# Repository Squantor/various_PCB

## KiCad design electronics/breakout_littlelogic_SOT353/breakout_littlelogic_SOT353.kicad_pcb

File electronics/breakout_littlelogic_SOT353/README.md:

# Little logic breakout for 5 pin SOT353 packages
Simple breakout board for little logic devices in SOT353 case.
## TODO's
Still some things need to be done:
* schematic entry 
* PCB layout
* Review with one night in between
* Produce at [OSHPARK](https://oshpark.com/)
* Assemble
* Test & characterise
* update Readme.md with pictures and BOM
## BOM
* any 5 pin little logic in SOT353 has this pinout with VDD/VSS in these positions

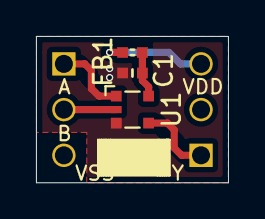
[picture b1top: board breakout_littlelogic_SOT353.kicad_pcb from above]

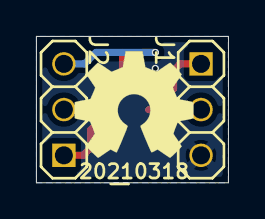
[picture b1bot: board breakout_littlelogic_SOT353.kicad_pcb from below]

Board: 2 copper layers, 10.7 x 8.1 mm, 8 parts (4 on the bottom side), 6 nets.

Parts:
C1: 1u; C_0402
FB1: 600; L_0402
J1, J2: Conn_01x03; Header-0254-1X03-H010
N1: 20210318; Label_Generic
N2: OHWLOGO; OSHW-Symbol_6.7x6mm_SilkScreen
N3: Type; Label_Note_small
U1: Generic_LL_5pin; SOT353

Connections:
/A: J1.1, U1.1
/B: J1.2, U1.2
/VDD: FB1.2, J2.3
/VSS: C1.2, J1.3, U1.3
/Y: J2.1, U1.4
unnamed: C1.1, FB1.1, U1.5

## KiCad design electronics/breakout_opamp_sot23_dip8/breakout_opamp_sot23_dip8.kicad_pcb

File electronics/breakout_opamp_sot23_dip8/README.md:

# SOT23-5 opamp to PDIP-8 converter
Small converter PCB that converts a SOT23-5 opamp to a PDIP-8 footprint
## TODO's
Still some things need to be done:
* Fill in this project description
* schematic entry 
* PCB layout
* Review with one night in between
* Produce at [OSHPARK](https://oshpark.com/)
* Assemble
* Test & characterise
* update Readme.md with pictures and BOM
## BOM
This is a list of hardware components. If just mentioned a generic component like a 1K 0402 resistor, just name it as such, free to substitute. If you need some special integrated IC's show some sources like Mouser, Digikey, Farnell, or LCSC
* Generic SOT23-5 opamp like LM321
## Pictures

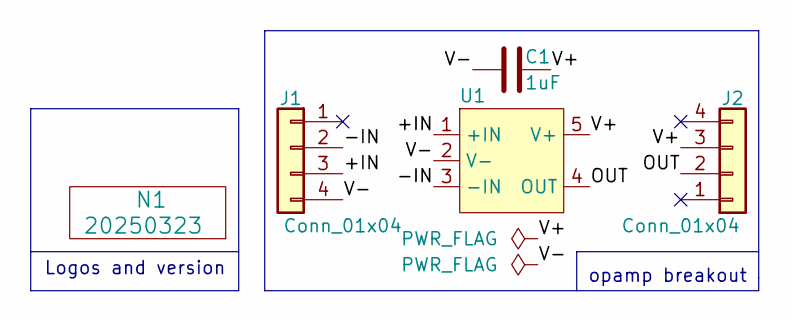
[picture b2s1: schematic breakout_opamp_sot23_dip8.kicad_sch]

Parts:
C1: 1uF; C_0805+0603
J1, J2: Conn_01x04; Header-0254-1X04-H010
N1: 20250323; Label_Generic
U1: SOT23-5-Microchip-OT

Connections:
/+IN: J1.3, U1.1 (+IN)
/-IN: J1.2, U1.3 (-IN)
/OUT: J2.2, U1.4 (OUT)
/V+: C1.2, J2.3, U1.5 (V+)
/V-: C1.1, J1.4, U1.2 (V-)

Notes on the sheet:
Logos and version
opamp breakout

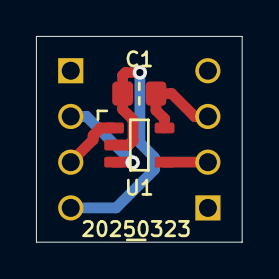
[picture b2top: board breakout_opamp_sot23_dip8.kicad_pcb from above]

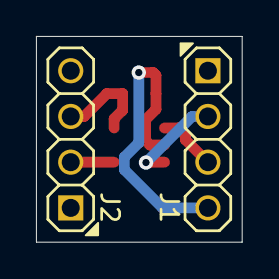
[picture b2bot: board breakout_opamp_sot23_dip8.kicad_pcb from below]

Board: 2 copper layers, 11.4 x 11.4 mm, 5 parts (2 on the bottom side), 5 nets.

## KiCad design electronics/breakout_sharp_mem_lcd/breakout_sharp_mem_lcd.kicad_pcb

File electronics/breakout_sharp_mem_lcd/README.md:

# Sharp memory LCD breakout board
Breakout board to test out sharp memory LCD support circuits.
## TODO's
* Review with one night in between
* Produce
* Assemble
* Test & characterise
* update Readme.md with pictures and BOM
## BOM
* [REG710NA-5/3K](https://www.lcsc.com/product-detail/DC-DC-Converters_Texas-Instruments-REG710NA-5-3K_C527422.html) 5V output regulated charge pump.
* Any sharp memory LCD, I get them at this [aliexpress store](https://www.aliexpress.com/store/5497024?spm=a2g0s.9042311.0.0.4f7e4c4d0shfdY).
* [THD0515-10CL-SN](https://www.lcsc.com/product-detail/FFC-FPC-Connectors_THD-THD0515-10CL-SN_C283142.html) flat flex connector

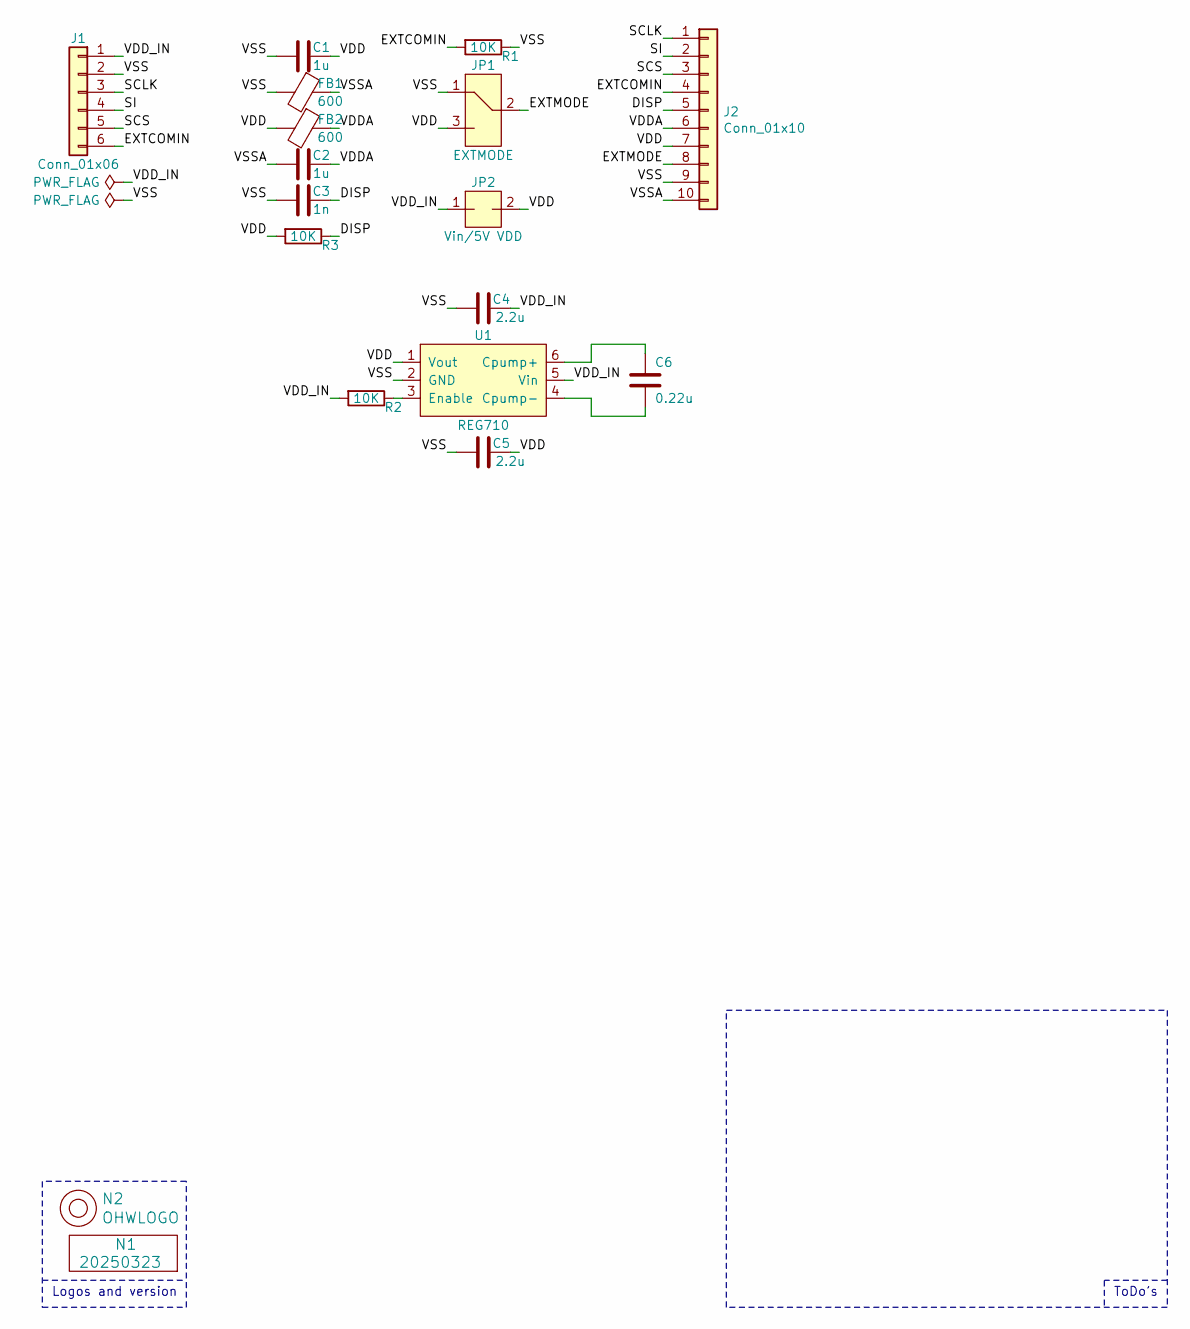
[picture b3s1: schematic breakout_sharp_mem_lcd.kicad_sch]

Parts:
C1, C2: 1u; C_0603
C3: 1n; C_0603
C4, C5: 2.2u; C_0603
C6: 0.22u; C_0603
FB1, FB2: 600; L_0603
J1: Conn_01x06; Header-0254-1X06-H010
J2: Conn_01x10; TE_1-1734839-0_1x10-1MP_P0.5mm_Horizontal
JP1: EXTMODE; solder_jumper_0402_3way_12conn
JP2: Vin/5V VDD; solder_jumper_0402_2way_noconn
N1: 20250323; Label_Generic
N2: OHWLOGO; OSHW-Symbol_6.7x6mm_SilkScreen
R1, R2, R3: 10K; R_0603_hand
U1: REG710; SOT23-6-HAND

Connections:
/DISP: C3.1, J2.5, R3.1
/EXTCOMIN: J1.6, J2.4, R1.2
/EXTMODE: J2.8, JP1.2
/SCLK: J1.3, J2.1
/SCS: J1.5, J2.3
/SI: J1.4, J2.2
/VDD: C1.1, C5.1, FB2.2, J2.7, JP1.3, JP2.2, R3.2, U1.1 (Vout)
/VDDA: C2.1, FB2.1, J2.6
/VDD_IN: C4.1, J1.1, JP2.1, R2.2, U1.5 (Vin)
/VSS: C1.2, C3.2, C4.2, C5.2, FB1.2, J1.2, J2.9, JP1.1, R1.1, U1.2 (GND)
/VSSA: C2.2, FB1.1, J2.10
unnamed: C6.1, U1.6 (Cpump+)
unnamed: C6.2, U1.4 (Cpump-)
unnamed: R2.1, U1.3 (Enable)

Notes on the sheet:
ToDo's
Logos and version

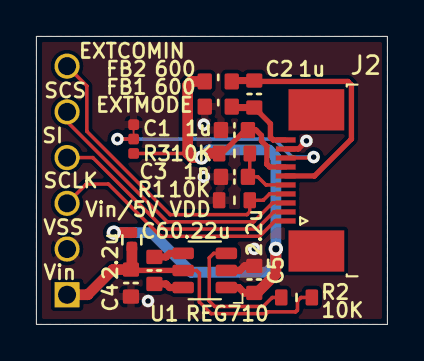
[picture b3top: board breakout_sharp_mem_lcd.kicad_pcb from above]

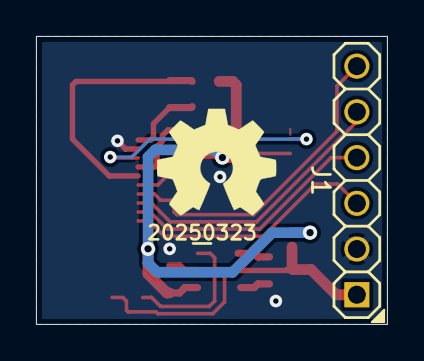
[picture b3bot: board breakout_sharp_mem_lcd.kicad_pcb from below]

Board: 2 copper layers, 19.5 x 16.0 mm, 18 parts (3 on the bottom side), 14 nets.
